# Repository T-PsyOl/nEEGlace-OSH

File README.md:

# nEEGlace-OpenHardware

nEEGlace is an open hardware platform for studying neural activity in everyday
environments. It is designed to enable long-term, wearable EEG recordings
combined with rich contextual data, such as binaural audio, while remaining
compact, reproducible, and extensible.

The project is developed at the Translational Psychology Lab,
at the Department of Psychology at the Carl von Ossietzky Universität Oldenburg.

## Motivation

Understanding brain activity outside the laboratory is essential for studying
natural cognition, perception, and behavior. However, conventional EEG systems
are typically bulky, restrictive, and optimized for short, controlled
experiments. As a result, they are poorly suited for long-term or
ecologically valid recordings and often lack information about the sensory and
environmental context in which neural signals are recorded.

nEEGlace addresses these limitations by integrating ear-EEG with additional
contextual sensors into a neck-worn, wearable system that can be used in
real-world settings.

## Scientific Background

nEEGlace-OpenHardware builds on several stages of previous work on mobile,
neck-worn EEG systems for studying brain activity beyond the laboratory.

An early precursor was used in a long-term mobile ear-EEG study on auditory
attention in everyday life. In that study, a mobile EEG amplifier was attached
to headphones worn around the neck, which were also used for sound presentation.
Participants wore the setup for several hours while performing auditory oddball
tasks in the laboratory and during normal office routines. This work showed that
long-term mobile EEG recordings can be used to study auditory processing in
everyday settings.
The study can be found here:

[Hölle, D., Meekes, J., & Bleichner, M. G. (2021). Mobile ear-EEG to study
auditory attention in everyday life. *Behavior Research Methods*, 53,
2025–2036.](https://doi.org/10.3758/s13428-021-01538-0)

Based on this experience, the original nEEGlace system was developed as a more
integrated neck-worn platform. It combined a commercial, research-grade EEG
amplifier with a commercial neck speaker, creating a compact system for mobile
EEG recordings with integrated sound presentation and contextual audio
recording.

The original nEEGlace project is documented in the previous repository:

[https://github.com/T-PsyOl/neeglace](https://github.com/T-PsyOl/neeglace)

The associated hardware metapaper was published in the *Journal of Open
Hardware*:

[Bleichner, M. G., & Emkes, R. (2020). Building an Ear-EEG System by Hacking a
Commercial Neck Speaker and a Commercial EEG Amplifier to Record Brain Activity
Beyond the Lab. *Journal of Open Hardware*, 4(1).](https://doi.org/10.5334/joh.25)

This nEEGlace version was subsequently used in a study on smartphone-based
ear-EEG for investigating sound processing in everyday life. In that work,
participants were equipped with the nEEGlace, a smartphone-based recording setup, and microphones for recording
the acoustic environment. The study demonstrated how mobile EEG recordings can
be combined with contextual sound information to investigate neural responses
to sounds in more naturalistic conditions.

The study is described here:

[Hölle, D., & Bleichner, M. G. (2023). Smartphone-based
ear-electroencephalography to study sound processing in everyday life.
*European Journal of Neuroscience*, 58(7), 3671–3685.](https://doi.org/10.1111/ejn.16124)

The current nEEGlace-OpenHardware platform continues this line of work. Whereas
the earlier systems relied on adapting and integrating commercial components,
nEEGlace-OpenHardware is designed as a reproducible, modular, and extensible
open-hardware platform. It retains the central scientific aim of recording
neural activity together with contextual information in everyday environments,
while making the system easier to document, reproduce, modify, and further
develop.

## System Overview
nEEGlace is designed around a modular, 3D-printable casing that can be worn around
the neck. The casing houses the core components required for mobile EEG and
contextual audio recording and provides a reproducible mechanical platform for
integrating different hardware configurations.

The system includes:

- **A neck-worn casing** that can be 3D printed and adapted to house different
  hardware components and configurations.
- **Electrode connectors** for connecting ear-EEG electrodes, such as cEEGrids,
  or other EEG electrode arrangements.
- **An EEG acquisition system** for recording neural activity during mobile
  measurements.
- **An audio processing board** for real-time audio processing, event
  extraction, and event injection into the EEG data stream.
- **Binaural microphones** for recording the acoustic environment from the
  wearer’s perspective.
- **A battery unit** that powers all components for several hours of mobile
  operation.

The system is modular by design. Components such as the EEG system, audio board,
microphones, battery unit, connectors, and casing parts can be modified,
replaced, or reconfigured without redesigning the full platform. This allows
nEEGlace to serve as a general neck-worn hardware platform for mobile
neurophysiology and context-aware sensing, rather than as a fixed device tied to
one specific hardware setup.

## Repository Structure

This repository contains all components required to build, program, and use the
nEEGlace system:
- assets/ Media files, figures, and illustrations
- docs/ Background documentation and design rationale
- firmware/ Low-level firmware for embedded components
- hardware/ Hardware documentation (electronics, BMS, casing, wiring)
- manufacturing/ Manufacturing files and production-related information
- software/ User-facing software, analysis tools, and utilities
- test/ Hardware and software tests and validation scripts

Each folder contains its own README with more detailed documentation.

## Design Principles

nEEGlace follows a small set of guiding principles:

- **Open hardware**: schematics, layouts, and designs are shared
- **Modularity**: hardware and software components are loosely coupled
- **Wearability**: suitable for long-term use in everyday environments
- **Context awareness**: neural data is recorded together with relevant
  environmental information

## Project Status

nEEGlace is an active research and development project.
The hardware and software described here reflect the current prototype and may
evolve over time. Contributions, feedback, and replication efforts are welcome.

For details on specific components, please start with the corresponding
subfolder.

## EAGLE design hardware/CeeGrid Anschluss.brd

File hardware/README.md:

# nEEGlace Hardware
This directory documents the complete hardware setup of the nEEGlace system.

The hardware integrates EEG acquisition, high-quality audio recording,
real-time processing, and battery-powered operation into a single wearable
device.

## System Overview

The nEEGlace hardware is built around the following core components:

- [Bela GEM Stereo](https://eu.shop.bela.io/products/bela-gem-stereo) for real-time audio and control
   - We originally used the Bela Mini; however, as it has been discontinued, we are transitioning to the Bela GEM Stereo.
- [OpenBCI Cyton (8-channel)](https://shop.openbci.com/products/cyton-biosensing-board-8-channel) or [Cyton + Daisy (16-channel)](https://shop.openbci.com/products/cyton-daisy-biosensing-boards-16-channel) for (ear)-EEG
- [Roland CS-10EM binaural microphones](https://proav.roland.com/de/products/proav_cs-10em/) for stereo audio
- **Battery Management System (BMS)** and rechargeable battery
- **Custom Bela Cape** for electrical integration
- **Wearable casing** and internal wiring

## Directory Structure

hardware/
├── BMS/
│   └── README.md
├── cape/
│   └── README.md
├── casing/
│   └── README.md
├── wiring/
│   └── README.md
└── README.md  ← you are here

Each subfolder documents one hardware module and its role in the overall system.

## Required Hardware Components

### 1. Processing and Control
- **Bela Gem Stereo**
  - Executes real-time audio and data acquisition code
  - Acts as the central control unit

- **Custom Bela Cape**
  - Interfaces Bela Mini with:
    - OpenBCI EEG amplifier
    - Roland CS-10EM microphones
    - Power system
  - Provides signal routing and mechanical mounting

### 2. EEG Acquisition
- **OpenBCI Cyton Biosensing Board (8-channel)**  
  *or*  
- **OpenBCI Cyton + Daisy Biosensing Boards (16-channel)**

- **EEG electrodes**
  - EEG electrodes
  - OpenBCI-compatible connectors and cables

### 3. Audio Acquisition
- **Roland CS-10EM binaural microphones**
  - In-ear stereo microphones
  - Connected to Bela Mini audio inputs

- **Audio cabling**
  - Stereo microphone cables

### 4. Power System
- **Rechargeable battery**
  - LiPo

- **Battery Management System (BMS)**
  - Battery charging
  - Electrical protection
  - Power distribution to Bela and peripherals

### 5. Wiring and Interconnection

### 6. Mechanical Components
- **nEEGlace casing**
  - Houses all electronic components
  - Designed for wearable, everyday use
- Fasteners and mounting elements

## Design Principles

The nEEGlace hardware follows these principles:

- **Open hardware**: all designs are shared and documented
- **Modularity**: individual components can be replaced or extended
- **Low-noise design**: separate EEG and audio signal paths
- **Wearability**: suitable for long-term, real-world recordings

## Status

This documentation reflects the current nEEGlace prototype.
Hardware components and interfaces may evolve as the project progresses.
Each submodule README documents its current state and known limitations.

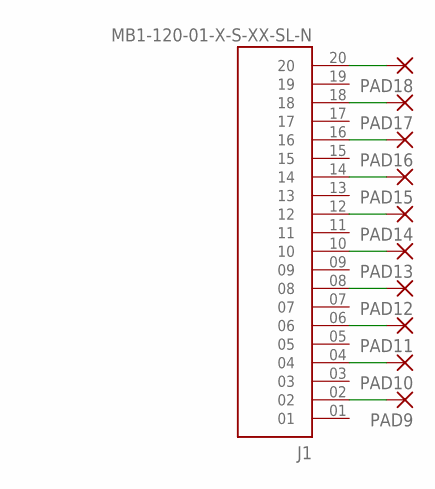
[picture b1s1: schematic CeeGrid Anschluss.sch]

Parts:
J1: MB1-120-01-X-S-XX-SL-N; SAMTEC_MB1-120-01-X-S-XX-SL-N
PAD9, PAD10, PAD11, PAD12, PAD13, PAD14, PAD15, PAD16, PAD17, PAD18: SMD2; SMD1,27-2,54

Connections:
unnamed: J1.20, PAD18.1
unnamed: J1.18, PAD17.1
unnamed: J1.16, PAD16.1
unnamed: J1.14, PAD15.1
unnamed: J1.12, PAD14.1
unnamed: J1.10, PAD13.1
unnamed: J1.08, PAD12.1
unnamed: J1.06, PAD11.1
unnamed: J1.04, PAD10.1
unnamed: J1.02, PAD9.1

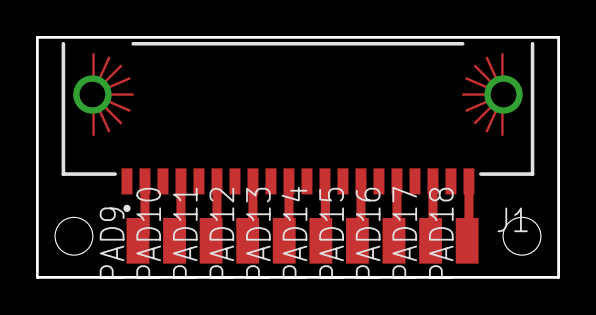
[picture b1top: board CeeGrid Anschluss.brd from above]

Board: 2 copper layers, 29.0 x 13.3 mm, 11 parts (0 on the bottom side), 10 nets.

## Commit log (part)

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2026-02-02 Rename PCB_PCB_BMS_nEEGlace_2_2026-01-31.json to PCB_BMS.json
2026-02-02 Rename PCB_PCB_BMS_nEEGlace_2_2026-01-31.pdf to PCB_BMS.pdf
2026-02-02 Rename hardware/BMS/LDO_MCP1700.pdf to hardware/BMS/Datasheets/LDO_MCP1700.pdf
2026-02-09 Added a hardware overview
2026-02-09 Enhance README with detailed project information
    Expanded the README to include motivation, system overview, repository structure, design principles, and project status.
2026-03-20 Revise hardware component names and descriptions
    Updated hardware components and design principles for clarity.
2026-03-27 Rename audio_onset_detection.cpp to audio_onset_detection.cpp
2026-04-15 Revise Readme.md for BMS project clarity
    Updated the Readme.md to enhance clarity and detail about the Battery Management System (BMS) for the nEEGlace wearable EEG platform, including system description, power architecture, safety features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
2026-04-15 Fix formatting in Readme.md for Overview section
2026-05-05 Adding rms computation
    Adding in the render function, line 211, computation of RMS.
    Also added the output of the RMS, when an onset is detected, in line 216.
2026-05-05 Adding csv file saving
    From line 57 to 60 added CSV logging variables
    In the setup function from line 155 to 163 added the setup for the CSV file.
    Added variable "detection" in line 216, so we can store it into the CSV file.
    In the render function from line 218 to 225 added the logging of the data to the CSV file.
    Also changed in line 228 the condition to the variable "detection".
    From line 301 to 304 added the closing of the CSV file.
2026-05-05 Added fft computation and README
    Implementation of an FFT calculation to display the frequency of the detected signal. Calculation performed using a circular buffer, with no data stored in the render function. The circular buffer is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
    The issue with the recording duration persists. Currently, it cannot be set to more than 300 seconds. This is due to suboptimal memory usage when saving the audio file. This is still being worked on.
2026-05-12 Writing constantly to .csv file
    Thats Abins work
2026-05-13 ADDING SCIENTIFIC BACKGROUND
2026-05-13 updated scientific background
2026-05-13 updated the system overview
2026-05-13 fixed the double heading
2026-05-18 Added 8 Freq. bands
    There is still a problem with the underrun.
2026-05-28 Add README for audio event detection implementation
    Added README.md for audio event detection code, detailing implementation, parameters, outputs, current status, limitations, and future improvements.
2026-06-04 Rename hardware/Samtec_PCB_3d.stl to hardware/3d files/Samtec_PCB_3d.stl
2026-06-04 Rename hardware/BMS/PickAndPlace_PCB_nEEGlace_BMS_4_2026-06-04.csv to hardware/BMS/PCB_Assembly_Files/PickAndPlace_PCB_nEEGlace_BMS.csv
2026-06-04 Rename hardware/BMS/BOM_nEEGlace_BMS_2026-06-04.csv to hardware/BMS/PCB_Assemble_Files/BOM_nEEGlace_BMScsv
2026-06-04 Rename BOM_nEEGlace_BMScsv to BOM_nEEGlace_BMScsv
2026-06-04 Rename Gerber_nEEGlace_BMS_PCB_nEEGlace_BMS_4_2026-06-04.zip to Gerber_nEEGlace_BMS.zip
2026-06-04 Rename PCB_PCB_nEEGlace_BMS_4_2026-06-04.pdf to PCB_nEEGlace_BMSpdf
2026-06-04 Rename PCB_nEEGlace_BMSpdf to PCB_nEEGlace_BMS.pdf
2026-06-04 Rename hardware/BMS/PCB_PCB_nEEGlace_BMS_4_2026-06-04.png to hardware/BMSPCB_nEEGlace_BMS.png
2026-06-04 Rename hardware/BMSPCB_nEEGlace_BMS.png to hardware/BMS/PCB_nEEGlace_BMS.png
2026-06-04 Rename Schematic_nEEGlace_BMS_2026-05-28 (1).pdf to Schematic_nEEGlace_BMS.pdf
2026-06-04 Rename hardware/BOM_Schematic1_Bela_Gem_Stereo_2026-06-04.csv to hardware/Bela Cape/PCB_Assembly_Files/BOM_Bela_Gem_Stereo.csv
2026-06-04 Rename PickAndPlace_Bela_Gem_Stereo_2026_06_04.csv to PickAndPlace_Bela_Cape.csv
2026-06-04 Add BOM_Bela_Cape.csv to PCB assembly files
2026-06-04 Rename PCB_Bela_Gem_Stereo_2026-06-04.png to PCB_Bela_Cape.png
2026-06-04 Rename InteractiveBOM_Bela_Gem_Stereo_2026-6-4.html to InteractiveBOM_Bela_Cape.html
2026-06-04 Rename Gerber_Bela_Gem_Stereo_2026-06-04.zip to Gerber_Bela_Cape.zip
2026-06-04 Rename hardware/CeeGrid Anschluss.brd to hardware/CEEgrids/CeeGrid Anschluss.brd
2026-06-04 Rename hardware/CeeGrid Anschluss.sch to hardware/CEEgrids/CeeGrid Anschluss.sch
2026-06-04 Rename hardware/L-Mic_PCB.zip to hardware/Mic_PCB/Left_Mic_Gerber_PCB.zip
2026-06-04 Rename hardware/R-Mic_PCB.zip to hardware/Mic_Zip/Right_Mic_Gerber_PCB.zip
2026-06-04 Rename Right_Mic_Gerber_PCB.zip to Right_Mic_Gerber_PCB.zip
2026-06-04 Rename SCH_Left_MIC_2026-06-04.pdf to Schematic_Left_MIC.pdf
2026-06-04 Rename SCH_Right_MIC_2026-06-04.pdf to Schematic_Right_MIC.pdf
2026-06-11 Rename hardware/BMS/BOM_nEEGlace_BMS.csv to hardware/BMS/Assemble files/BOM_nEEGlace_BMS.csv
2026-06-11 Rename BOM_nEEGlace_BMS.csv to BOM_nEEGlace_BMS.csv
2026-06-11 Rename PickAndPlace_PCB_nEEGlace_BMS.csv file
2026-06-11 Rename PCB_PCB_nEEGlace_BMS_4_2026-06-11.pdf to PCB_nEEGlace_BMS.pdf
2026-06-11 Rename README.md to README.md
2026-06-11 Rename syncBela.m to syncBela.m
2026-06-15 Rename hardware/3D_Connector_PCB_.step to hardware/Connector_PCB/3D_Connector_PCB_.step
2026-06-15 Rename hardware/BOM_Schematic3_Connector_PCB_2026-06-12.csv to hardware/Connector_PCB/BOM_Schematic3_Connector_PCB_2026-06-12.csv
2026-06-15 Rename hardware/Gerber_Connector_PCB.zip to hardware/Connector_PCB/Gerber_Connector_PCB.zip
2026-06-15 Rename hardware/PickAndPlace_Connector_PCB.csv to hardware/Connector_PCB/PickAndPlace_Connector_PCB.csv
2026-06-15 Rename hardware/odb++_pcb_Connector.tgz to hardware/Connector_PCB/odb++_pcb_Connector.tgz
2026-06-15 Rename hardware/BOM_Mic_PCB.csv to hardware/MIC/BOM_Mic_PCB.csv
2026-06-23 Rename hardware/CEEgrids/BOM_CEEgrids.csv to hardware/CEEgrids/Assembly files/BOM_CEEgrids.csv
2026-06-23 Rename hardware/CEEgrids/PickAndPlace_CeeGrid.csv to hardware/CEEgrids/Assembly Files/PickAndPlace_CeeGrid.csv
2026-06-23 Rename PickAndPlace_CeeGrid.csv to PickAndPlace_CeeGrid.csv
2026-06-23 Rename hardware/MIC/BOM_Mic_PCB.csv to hardware/MIC/Assembly files/BOM_Mic_PCB.csv
2026-06-23 Rename hardware/MIC/odb++_Mic_PCB.tgz to hardware/MIC/Assembly file/odb++_Mic_PCB.tgz
2026-06-23 Rename odb++_Mic_PCB.tgz to odb++_Mic_PCB.tgz
2026-06-23 Rename hardware/MIC/PickAndPlace_Mic_PCB.csv to hardware/MIC/Assembly files/PickAndPlace_Mic_PCB.csv
2026-06-23 Rename hardware/Connector_PCB/BOM_Schematic3_Connector_PCB_2026-06-12.csv to hardware/Connector_PCB/Assembly files/BOM_Schematic3_Connector_PCB_2026-06-12.csv
2026-06-23 Add PickAndPlace_Connector_PCB.csv file
2026-06-23 Rename hardware/Connector_PCB/odb++_pcb_Connector.tgz to hardware/Connector_PCB/Assembly files/odb++_pcb_Connector.tgz
2026-06-23 Delete hardware overview diagram from Readme
    Removed hardware overview diagram from Readme.MD
2026-06-23 Create comprehensive README for Bela Cape
    Added detailed documentation for the Bela Cape, including an overview, repository structure, component references, and design rationale.
2026-06-23 Create README for CeeGrid Anschluss PCB
    Added documentation for the CeeGrid Anschluss PCB, detailing its purpose, structure, and usage.
2026-06-23 Rename DXF_Schematic_nEEGlace_2026-6-24.zip to DXF_Schematic_nEEGlace.zip
2026-06-25 Rename software/BELA Scripts/audio_onset_detection.cpp to software/BELA Scripts/others/audio_onset_detection.cpp
2026-06-25 Create Makefile
